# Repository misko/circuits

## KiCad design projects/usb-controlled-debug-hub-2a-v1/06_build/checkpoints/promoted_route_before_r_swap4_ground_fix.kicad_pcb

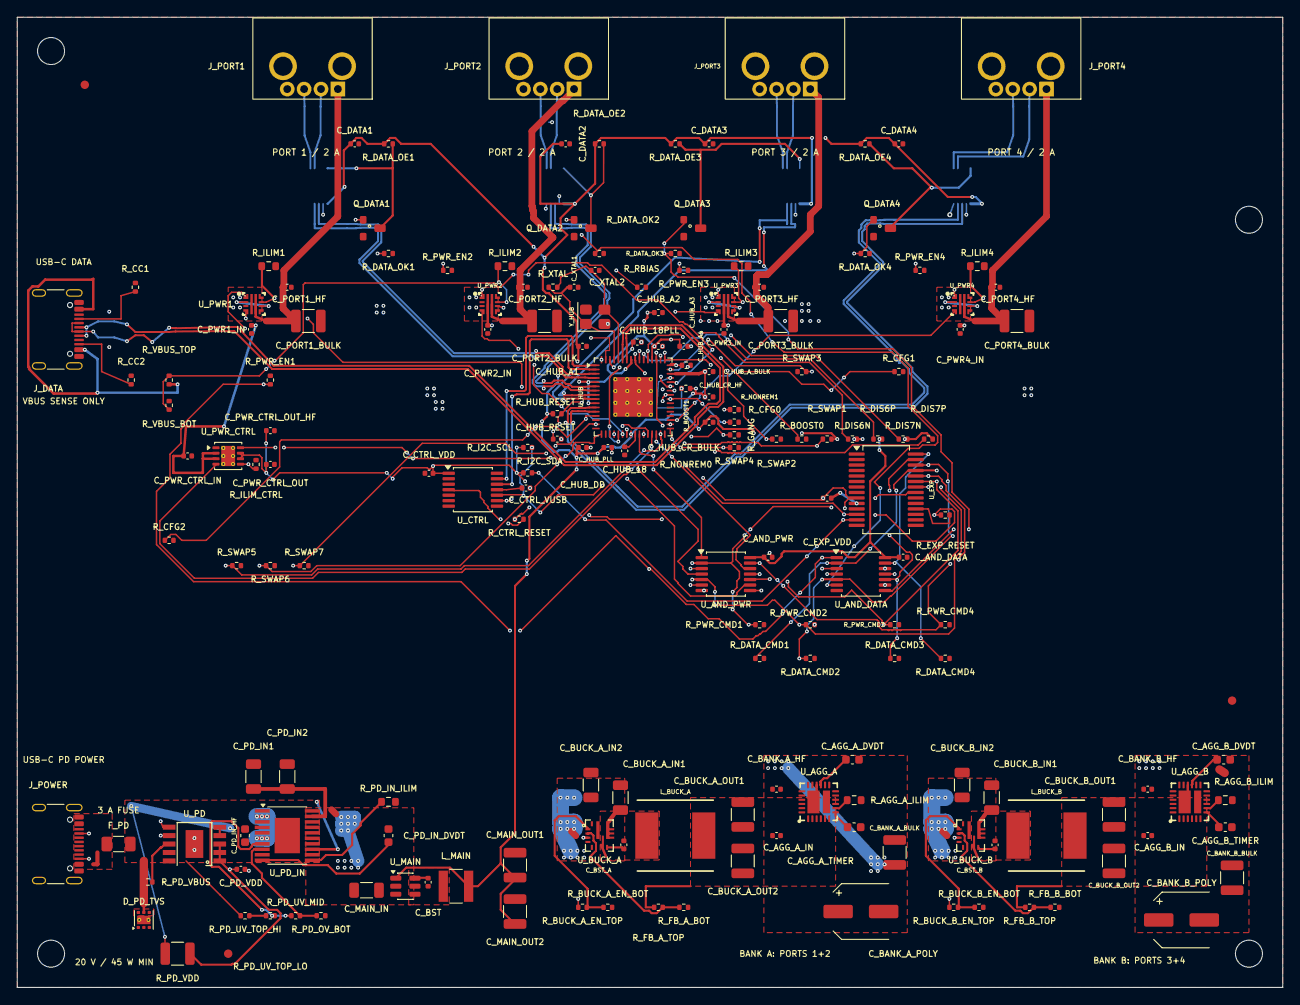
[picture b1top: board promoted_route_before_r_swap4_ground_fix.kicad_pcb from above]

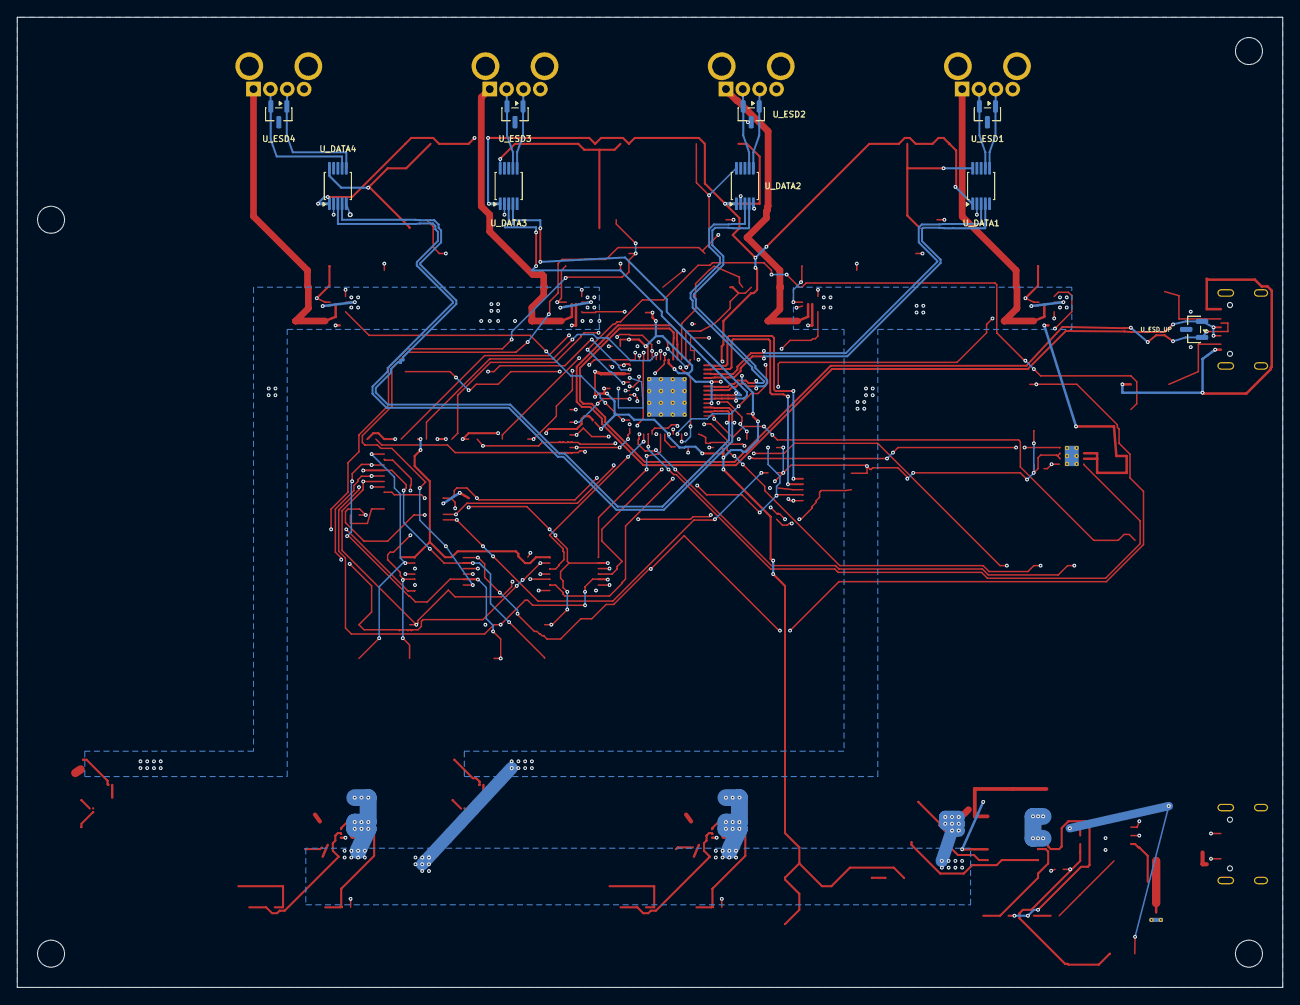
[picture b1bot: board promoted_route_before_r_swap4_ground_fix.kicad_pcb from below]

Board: 4 copper layers, 150.0 x 115.0 mm, 190 parts (9 on the bottom side), 129 nets.

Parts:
C_AGG_A_DVDT: 3.3nF; C_0603_1608Metric
C_AGG_A_IN: 100nF; C_0402_1005Metric
C_AGG_A_TIMER: 6.8nF; C_0603_1608Metric
C_AGG_B_DVDT: 3.3nF; C_0603_1608Metric
C_AGG_B_IN: 100nF; C_0402_1005Metric
C_AGG_B_TIMER: 6.8nF; C_0603_1608Metric
C_AND_DATA: 100nF; C_0402_1005Metric
C_AND_PWR: 100nF; C_0402_1005Metric
C_BANK_A_BULK: 22uF; C_1210_3225Metric
C_BANK_A_HF: 100nF; C_0402_1005Metric
C_BANK_A_POLY: 180uF; Panasonic_C6_6.3x5.9
C_BANK_B_BULK: 22uF; C_1210_3225Metric
C_BANK_B_HF: 100nF; C_0402_1005Metric
C_BANK_B_POLY: 180uF; Panasonic_C6_6.3x5.9
C_BST: 100nF; C_0402_1005Metric
C_BST_A: 100nF; C_0402_1005Metric
C_BST_B: 100nF; C_0402_1005Metric
C_BUCK_A_IN1, C_BUCK_A_IN2: 10uF; C_1206_3216Metric
C_BUCK_A_OUT1, C_BUCK_A_OUT2: 22uF; C_1210_3225Metric
C_BUCK_B_IN1, C_BUCK_B_IN2: 10uF; C_1206_3216Metric
C_BUCK_B_OUT1, C_BUCK_B_OUT2: 22uF; C_1210_3225Metric
C_CTRL_VDD: 100nF; C_0402_1005Metric
C_CTRL_VUSB: 330nF; C_0402_1005Metric
C_DATA1, C_DATA2, C_DATA3, C_DATA4: 100nF; C_0402_1005Metric
C_EXP_VDD: 100nF; C_0402_1005Metric
C_HUB_18, C_HUB_18PLL: 1uF; C_0402_1005Metric
C_HUB_A1, C_HUB_A2, C_HUB_A3, C_HUB_A4: 100nF; C_0402_1005Metric
C_HUB_A_BULK: 1uF; C_0402_1005Metric
C_HUB_CR_BULK: 1uF; C_0402_1005Metric
C_HUB_CR_HF: 100nF; C_0402_1005Metric
C_HUB_DD: 100nF; C_0402_1005Metric
C_HUB_PLL: 100nF; C_0402_1005Metric
C_HUB_RESET: 1uF; C_0402_1005Metric
C_MAIN_IN: 10uF; C_1206_3216Metric
C_MAIN_OUT1, C_MAIN_OUT2: 22uF; C_1210_3225Metric
C_PD_IN1, C_PD_IN2: 10uF; C_1206_3216Metric
C_PD_IN_DVDT: 3.3nF; C_0603_1608Metric
C_PD_IN_HF: 1uF; C_0603_1608Metric
C_PD_VDD: 1uF; C_0402_1005Metric
C_PORT1_BULK, C_PORT2_BULK, C_PORT3_BULK, C_PORT4_BULK: 22uF; C_1210_3225Metric
C_PORT1_HF, C_PORT2_HF, C_PORT3_HF, C_PORT4_HF: 100nF; C_0402_1005Metric
C_PWR1_IN, C_PWR2_IN, C_PWR3_IN, C_PWR4_IN: 100nF; C_0402_1005Metric
C_PWR_CTRL_IN: 100nF; C_0402_1005Metric
C_PWR_CTRL_OUT: 1uF; C_0402_1005Metric
C_PWR_CTRL_OUT_HF: 100nF; C_0402_1005Metric
C_XTAL1, C_XTAL2: 18pF; C_0402_1005Metric
D_PD_TVS: C523793; WSON-6-1EP_2x2mm_P0.65mm_EP1x1.6mm_ThermalVias
FID1, FID2, FID3: Fiducial_1mm_Mask2mm
F_PD: C14165; Fuse_1206_3216Metric
H1, H2, H3, H4: MountingHole_3.2mm_M3
J_DATA: C165948; TYPE-C-31-M-12_Datasheet
J_PORT1, J_PORT2, J_PORT3, J_PORT4: USB1130-15-A; USB_A_GCT_USB1130-15-A_Horizontal
J_POWER: C165948; TYPE-C-31-M-12_Datasheet
L_BUCK_A: C17700166; Sunlord_MWSA0804S
L_BUCK_B: C17700166; Sunlord_MWSA0804S
L_MAIN: C15269; Sunlord_SWPA4030S
Q_DATA1, Q_DATA2, Q_DATA3, Q_DATA4: C85047; Diodes_SOT23_2N7002K
R_AGG_A_ILIM: 300Ω; R_0603_1608Metric
R_AGG_B_ILIM: 300Ω; R_0603_1608Metric
R_BOOST0, R_BOOST1: 10kΩ; R_0402_1005Metric
R_BUCK_A_EN_BOT: 27.4kΩ; R_0402_1005Metric
R_BUCK_A_EN_TOP: 200kΩ; R_0402_1005Metric
R_BUCK_B_EN_BOT: 27.4kΩ; R_0402_1005Metric
R_BUCK_B_EN_TOP: 200kΩ; R_0402_1005Metric
R_CC1, R_CC2: 5.1kΩ; R_0402_1005Metric
R_CFG0, R_CFG1, R_CFG2: 10kΩ; R_0402_1005Metric
R_CTRL_RESET: 10kΩ; R_0402_1005Metric
R_DATA_CMD1, R_DATA_CMD2, R_DATA_CMD3, R_DATA_CMD4: 10kΩ; R_0402_1005Metric
R_DATA_OE1, R_DATA_OE2, R_DATA_OE3, R_DATA_OE4: 10kΩ; R_0402_1005Metric
R_DATA_OK1, R_DATA_OK2, R_DATA_OK3, R_DATA_OK4: 10kΩ; R_0402_1005Metric
R_DIS6N, R_DIS6P, R_DIS7N, R_DIS7P: 10kΩ; R_0402_1005Metric
R_EXP_RESET: 10kΩ; R_0402_1005Metric
R_FB_A_BOT: 10kΩ; R_0402_1005Metric
R_FB_A_TOP: 75kΩ; R_0402_1005Metric
R_FB_B_BOT: 10kΩ; R_0402_1005Metric
R_FB_B_TOP: 75kΩ; R_0402_1005Metric
R_GANG: 10kΩ; R_0402_1005Metric
R_HUB_RESET: 10kΩ; R_0402_1005Metric
R_I2C_SCL, R_I2C_SDA: 4.7kΩ; R_0402_1005Metric
R_ILIM1, R_ILIM2, R_ILIM3, R_ILIM4: 1.4kΩ; R_0603_1608Metric
R_ILIM_CTRL: 187kΩ; R_0402_1005Metric
R_NONREM0, R_NONREM1: 10kΩ; R_0402_1005Metric
R_PD_IN_ILIM: 5.9kΩ; R_0603_1608Metric
R_PD_OV_BOT: 51kΩ; R_0402_1005Metric
R_PD_UV_MID: 20kΩ; R_0402_1005Metric
R_PD_UV_TOP_HI: 910kΩ; R_0402_1005Metric
R_PD_UV_TOP_LO: 22kΩ; R_0402_1005Metric
R_PD_VBUS: 10kΩ; R_0402_1005Metric
R_PD_VDD: 1kΩ; R_1210_3225Metric
R_PWR_CMD1, R_PWR_CMD2, R_PWR_CMD3, R_PWR_CMD4: 10kΩ; R_0402_1005Metric
R_PWR_EN1, R_PWR_EN2, R_PWR_EN3, R_PWR_EN4: 10kΩ; R_0402_1005Metric
R_RBIAS: 12kΩ; R_0402_1005Metric
R_SWAP1, R_SWAP2, R_SWAP3, R_SWAP4, R_SWAP5, R_SWAP6, R_SWAP7: 100kΩ; R_0402_1005Metric
R_VBUS_BOT: 100kΩ; R_0402_1005Metric
R_VBUS_TOP: 47kΩ; R_0402_1005Metric
R_XTAL: 1MΩ; R_0402_1005Metric
U_AGG_A: C2155765; TI_TPS25982_RGE0024_SplitPad_ThermalVias
U_AGG_B: C2155765; TI_TPS25982_RGE0024_SplitPad_ThermalVias
U_AND_DATA: C6053; TSSOP-14_4.4x5mm_P0.65mm
U_AND_PWR: C6053; TSSOP-14_4.4x5mm_P0.65mm
U_BUCK_A: C841386; TI_RPA0010A_VQFN-HR-10_3x3mm
U_BUCK_B: C841386; TI_RPA0010A_VQFN-HR-10_3x3mm
U_CTRL: C130462; TSSOP-14_4.4x5mm_P0.65mm
U_DATA1, U_DATA2, U_DATA3, U_DATA4: C11355; MSOP-10_3x3mm_P0.5mm
U_ESD1, U_ESD2, U_ESD3, U_ESD4: C3709087; SOT-23
U_ESD_UP: C3709087; SOT-23
U_EXP: C558584; SSOP-28_5.3x10.2mm_P0.65mm
U_HUB: C478081; QFN-64-1EP_9x9mm_P0.5mm_EP4.7x4.7mm_ThermalVias
U_MAIN: C5248536; TSOT-23-6
U_PD: C970725; WCH_CH224K_ESSOP10_EP
U_PD_IN: C1849461; Texas_PWP0020A
U_PWR1, U_PWR2, U_PWR3, U_PWR4: C3662799; TI_RPW0010A_VQFN-HR-10_2x2mm_P0.45mm
U_PWR_CTRL: C130056; VSON-8-1EP_3x3mm_P0.65mm_EP1.65x2.4mm_ThermalVias
Y_HUB: C70590; Crystal_SMD_3225-4Pin_3.2x2.5mm

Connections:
3V3_MAIN: C_AND_DATA.1, C_AND_PWR.1, C_DATA1.1, C_DATA2.1, C_DATA3.1, C_DATA4.1, C_HUB_A1.1, C_HUB_A2.1, C_HUB_A3.1, C_HUB_A4.1, C_HUB_A_BULK.1, C_HUB_CR_BULK.1, C_HUB_CR_HF.1, C_HUB_DD.1, C_HUB_PLL.1, C_MAIN_OUT1.1, C_MAIN_OUT2.1, L_MAIN.2, R_DATA_OE1.1, R_DATA_OE2.1, R_DATA_OE3.1, R_DATA_OE4.1, R_DIS6N.1, R_DIS6P.1, R_DIS7N.1, R_DIS7P.1, R_HUB_RESET.1, R_NONREM0.1, R_SWAP1.2, U_AND_DATA.14, U_AND_PWR.14, U_DATA1.1, U_DATA2.1, U_DATA3.1, U_DATA4.1, U_HUB.5, U_HUB.10, U_HUB.24, U_HUB.46, U_HUB.52, U_HUB.57, U_HUB.64, U_MAIN.1
AGG_A_DVDT: C_AGG_A_DVDT.1, U_AGG_A.15
AGG_A_ILIM: R_AGG_A_ILIM.1, U_AGG_A.8
AGG_A_TIMER: C_AGG_A_TIMER.1, U_AGG_A.7
AGG_B_DVDT: C_AGG_B_DVDT.1, U_AGG_B.15
AGG_B_ILIM: R_AGG_B_ILIM.1, U_AGG_B.8
AGG_B_TIMER: C_AGG_B_TIMER.1, U_AGG_B.7
BOOT_A: C_BST_A.1, U_BUCK_A.7
BOOT_B: C_BST_B.1, U_BUCK_B.7
BST_3V3: C_BST.1, U_MAIN.6
BUCK_A_EN: R_BUCK_A_EN_BOT.1, R_BUCK_A_EN_TOP.2, U_BUCK_A.1
BUCK_B_EN: R_BUCK_B_EN_BOT.1, R_BUCK_B_EN_TOP.2, U_BUCK_B.1
CTRL_RESET_N: R_CTRL_RESET.2, U_CTRL.4
CTRL_VUSB_3V3: C_CTRL_VUSB.1, U_CTRL.11
DATA_CC1: J_DATA.A5, R_CC1.1
DATA_CC2: J_DATA.B5, R_CC2.1
DATA_CMD1: R_DATA_CMD1.1, U_AND_DATA.2, U_EXP.25
DATA_CMD2: R_DATA_CMD2.1, U_AND_DATA.5, U_EXP.26
DATA_CMD3: R_DATA_CMD3.1, U_AND_DATA.10, U_EXP.27
DATA_CMD4: R_DATA_CMD4.1, U_AND_DATA.13, U_EXP.28
DATA_OE1_N: Q_DATA1.3, R_DATA_OE1.2, U_DATA1.10
DATA_OE2_N: Q_DATA2.3, R_DATA_OE2.2, U_DATA2.10
DATA_OE3_N: Q_DATA3.3, R_DATA_OE3.2, U_DATA3.10
DATA_OE4_N: Q_DATA4.3, R_DATA_OE4.2, U_DATA4.10
DATA_OK1: Q_DATA1.1, R_DATA_OK1.1, U_AND_DATA.3
DATA_OK2: Q_DATA2.1, R_DATA_OK2.1, U_AND_DATA.6
DATA_OK3: Q_DATA3.1, R_DATA_OK3.1, U_AND_DATA.8
DATA_OK4: Q_DATA4.1, R_DATA_OK4.1, U_AND_DATA.11
EXP_RESET_N: R_EXP_RESET.2, U_EXP.18
FB_A: R_FB_A_BOT.1, R_FB_A_TOP.2, U_BUCK_A.2
FB_B: R_FB_B_BOT.1, R_FB_B_TOP.2, U_BUCK_B.2
GND: C_AGG_A_DVDT.2, C_AGG_A_IN.2, C_AGG_A_TIMER.2, C_AGG_B_DVDT.2, C_AGG_B_IN.2, C_AGG_B_TIMER.2, C_AND_DATA.2, C_AND_PWR.2, C_BANK_A_BULK.2, C_BANK_A_HF.2, C_BANK_A_POLY.2, C_BANK_B_BULK.2, C_BANK_B_HF.2, C_BANK_B_POLY.2, C_BUCK_A_IN1.2, C_BUCK_A_IN2.2, C_BUCK_A_OUT1.2, C_BUCK_A_OUT2.2, C_BUCK_B_IN1.2, C_BUCK_B_IN2.2, C_BUCK_B_OUT1.2, C_BUCK_B_OUT2.2, C_CTRL_VDD.2, C_CTRL_VUSB.2, C_DATA1.2, C_DATA2.2, C_DATA3.2, C_DATA4.2, C_EXP_VDD.2, C_HUB_18.2, C_HUB_18PLL.2, C_HUB_A1.2, C_HUB_A2.2, C_HUB_A3.2, C_HUB_A4.2, C_HUB_A_BULK.2, C_HUB_CR_BULK.2, C_HUB_CR_HF.2, C_HUB_DD.2, C_HUB_PLL.2, C_HUB_RESET.2, C_MAIN_IN.2, C_MAIN_OUT1.2, C_MAIN_OUT2.2, C_PD_IN1.2, C_PD_IN2.2, C_PD_IN_DVDT.2, C_PD_IN_HF.2, C_PD_VDD.2, C_PORT1_BULK.2, C_PORT1_HF.2, C_PORT2_BULK.2, C_PORT2_HF.2, C_PORT3_BULK.2, C_PORT3_HF.2, C_PORT4_BULK.2, C_PORT4_HF.2, C_PWR1_IN.2, C_PWR2_IN.2, C_PWR3_IN.2, C_PWR4_IN.2, C_PWR_CTRL_IN.2, C_PWR_CTRL_OUT.2, C_PWR_CTRL_OUT_HF.2, C_XTAL1.2, C_XTAL2.2, D_PD_TVS.1, D_PD_TVS.2, D_PD_TVS.3, D_PD_TVS.7, J_DATA.A1, J_DATA.A12, J_DATA.B1, J_DATA.B12, J_DATA.SH, J_PORT1.4, J_PORT1.5, J_PORT2.4, J_PORT2.5, J_PORT3.4, J_PORT3.5, J_PORT4.4, J_PORT4.5, J_POWER.A1, J_POWER.A12, J_POWER.B1, J_POWER.B12, J_POWER.SH, Q_DATA1.2, Q_DATA2.2, Q_DATA3.2, Q_DATA4.2, R_AGG_A_ILIM.2, R_AGG_B_ILIM.2, R_BOOST0.2, R_BOOST1.2, R_BUCK_A_EN_BOT.2, R_BUCK_B_EN_BOT.2, R_CC1.2, R_CC2.2, R_CFG0.2, R_CFG1.2, R_CFG2.2, R_DATA_CMD1.2, R_DATA_CMD2.2, R_DATA_CMD3.2, R_DATA_CMD4.2, R_DATA_OK1.2, R_DATA_OK2.2, R_DATA_OK3.2, R_DATA_OK4.2, R_FB_A_BOT.2, R_FB_B_BOT.2, R_GANG.2, R_ILIM1.2, R_ILIM2.2, R_ILIM3.2, R_ILIM4.2, R_ILIM_CTRL.2, R_NONREM1.2, R_PD_IN_ILIM.2, R_PD_OV_BOT.2, R_PWR_CMD1.2, R_PWR_CMD2.2, R_PWR_CMD3.2, R_PWR_CMD4.2, R_PWR_EN1.2, R_PWR_EN2.2, R_PWR_EN3.2, R_PWR_EN4.2, R_RBIAS.2, R_SWAP2.2, R_SWAP3.2, R_SWAP4.2, R_SWAP5.2, R_SWAP6.2, R_SWAP7.2, R_VBUS_BOT.2, U_AGG_A.4, U_AGG_A.5, U_AGG_A.10, U_AGG_A.11, U_AGG_A.12, U_AGG_A.14, U_AGG_A.26, U_AGG_B.4, U_AGG_B.5, U_AGG_B.10, U_AGG_B.11, U_AGG_B.12, U_AGG_B.14, U_AGG_B.26, U_AND_DATA.7, U_AND_PWR.7, U_BUCK_A.3, U_BUCK_A.9, U_BUCK_A.10, U_BUCK_B.3, U_BUCK_B.9, U_BUCK_B.10, U_CTRL.14, U_DATA1.2, U_DATA1.5, U_DATA2.2, U_DATA2.5, U_DATA3.2, U_DATA3.5, U_DATA4.2, U_DATA4.5, U_ESD1.3, U_ESD2.3, U_ESD3.3, U_ESD4.3, U_ESD_UP.3, U_EXP.10, U_EXP.15, U_EXP.16, U_EXP.17, U_HUB.65, U_MAIN.4, U_PD.9, U_PD.11, U_PD_IN.9, U_PD_IN.12, U_PD_IN.21, U_PWR1.2, U_PWR1.8, U_PWR2.2, U_PWR2.8, U_PWR3.2, U_PWR3.8, U_PWR4.2, U_PWR4.8, U_PWR_CTRL.1, U_PWR_CTRL.9, Y_HUB.2, Y_HUB.4
HUB_BOOST0: R_BOOST0.1, U_HUB.50
HUB_BOOST1: R_BOOST1.1, U_HUB.48
HUB_CFG0: R_CFG0.1, U_HUB.41
HUB_CFG1: R_CFG1.1, U_HUB.42
HUB_CFG2: R_CFG2.1, U_HUB.13
HUB_DIS6_N: R_DIS6N.2, U_HUB.53
HUB_DIS6_P: R_DIS6P.2, U_HUB.54
HUB_DIS7_N: R_DIS7N.2, U_HUB.55
HUB_DIS7_P: R_DIS7P.2, U_HUB.56
HUB_GANG: R_GANG.1, U_HUB.34
HUB_NONREM0: R_NONREM0.2, U_HUB.45
HUB_NONREM1: R_NONREM1.1, U_HUB.40
HUB_OCS1_N: U_HUB.28, U_PWR_CTRL.8
HUB_OCS2_N: U_HUB.27, U_PWR1.4
HUB_OCS3_N: U_HUB.22, U_PWR2.4
HUB_OCS4_N: U_HUB.21, U_PWR3.4
HUB_OCS5_N: U_HUB.35, U_PWR4.4
HUB_PRTPWR1: U_HUB.29, U_PWR_CTRL.4
HUB_PRTPWR2: U_AND_PWR.1, U_HUB.26
HUB_PRTPWR3: U_AND_PWR.4, U_HUB.23
HUB_PRTPWR4: U_AND_PWR.9, U_HUB.20
HUB_PRTPWR5: U_AND_PWR.12, U_HUB.30
HUB_RESET_N: C_HUB_RESET.1, R_HUB_RESET.2, U_HUB.43
HUB_SWAP1: R_SWAP1.1, U_HUB.51
HUB_SWAP2: R_SWAP2.1, U_HUB.49
HUB_SWAP3: R_SWAP3.1, U_HUB.47
HUB_SWAP4: R_SWAP4.1, U_HUB.33
HUB_SWAP5: R_SWAP5.1, U_HUB.31
HUB_SWAP6: R_SWAP6.1, U_HUB.17
HUB_SWAP7: R_SWAP7.1, U_HUB.15
HUB_VBUS_SENSE: R_VBUS_BOT.1, R_VBUS_TOP.2, U_HUB.44
HUB_VDD18: C_HUB_18.1, U_HUB.25
HUB_VDD18PLL: C_HUB_18PLL.1, U_HUB.62
I2C_SCL: R_I2C_SCL.2, U_CTRL.10, U_EXP.12
I2C_SDA: R_I2C_SDA.2, U_CTRL.9, U_EXP.13
ILIM1: R_ILIM1.1, U_PWR1.9
ILIM2: R_ILIM2.1, U_PWR2.9
ILIM3: R_ILIM3.1, U_PWR3.9
ILIM4: R_ILIM4.1, U_PWR4.9
ILIM_CTRL: R_ILIM_CTRL.1, U_PWR_CTRL.5
MGMT_N: U_CTRL.12, U_HUB.2
MGMT_P: U_CTRL.13, U_HUB.1
P1_HUB_N: U_DATA1.3, U_HUB.3
P1_HUB_P: U_DATA1.4, U_HUB.4
P1_PORT_N: J_PORT1.2, U_DATA1.7, U_ESD1.2
P1_PORT_P: J_PORT1.3, U_DATA1.6, U_ESD1.1
P2_HUB_N: U_DATA2.3, U_HUB.6
P2_HUB_P: U_DATA2.4, U_HUB.7
P2_PORT_N: J_PORT2.2, U_DATA2.7, U_ESD2.2
P2_PORT_P: J_PORT2.3, U_DATA2.6, U_ESD2.1
P3_HUB_N: U_DATA3.3, U_HUB.8
P3_HUB_P: U_DATA3.4, U_HUB.9
P3_PORT_N: J_PORT3.2, U_DATA3.7, U_ESD3.2
P3_PORT_P: J_PORT3.3, U_DATA3.6, U_ESD3.1
P4_HUB_N: U_DATA4.3, U_HUB.11
P4_HUB_P: U_DATA4.4, U_HUB.12
P4_PORT_N: J_PORT4.2, U_DATA4.7, U_ESD4.2
P4_PORT_P: J_PORT4.3, U_DATA4.6, U_ESD4.1
P5V_A_PROTECTED: C_BANK_A_BULK.1, C_BANK_A_HF.1, C_BANK_A_POLY.1, C_PWR1_IN.1, C_PWR2_IN.1, C_PWR_CTRL_IN.1, U_AGG_A.17, U_AGG_A.18, U_AGG_A.19, U_AGG_A.20, U_AGG_A.21, U_AGG_A.22, U_AGG_A.23, U_AGG_A.24, U_PWR1.5, U_PWR2.5, U_PWR_CTRL.2, U_PWR_CTRL.3
P5V_BANK_A: C_AGG_A_IN.1, C_BUCK_A_OUT1.1, C_BUCK_A_OUT2.1, L_BUCK_A.2, R_FB_A_TOP.1, U_AGG_A.1, U_AGG_A.2, U_AGG_A.3, U_AGG_A.6, U_AGG_A.16, U_AGG_A.25
P5V_BANK_B: C_AGG_B_IN.1, C_BUCK_B_OUT1.1, C_BUCK_B_OUT2.1, L_BUCK_B.2, R_FB_B_TOP.1, U_AGG_B.1, U_AGG_B.2, U_AGG_B.3, U_AGG_B.6, U_AGG_B.16, U_AGG_B.25
P5V_B_PROTECTED: C_BANK_B_BULK.1, C_BANK_B_HF.1, C_BANK_B_POLY.1, C_PWR3_IN.1, C_PWR4_IN.1, U_AGG_B.17, U_AGG_B.18, U_AGG_B.19, U_AGG_B.20, U_AGG_B.21, U_AGG_B.22, U_AGG_B.23, U_AGG_B.24, U_PWR3.5, U_PWR4.5
PD_CC1: J_POWER.A5, U_PD.7
PD_CC2: J_POWER.B5, U_PD.6
PD_IN_DVDT: C_PD_IN_DVDT.1, U_PD_IN.10
PD_IN_ILIM: R_PD_IN_ILIM.1, U_PD_IN.11
PD_IN_OV: R_PD_OV_BOT.1, R_PD_UV_MID.2, U_PD_IN.8
PD_IN_UV: R_PD_UV_MID.1, R_PD_UV_TOP_LO.2, U_PD_IN.7
PD_PROTO: U_PD.4, U_PD.5
PD_UV_TOP_MID: R_PD_UV_TOP_HI.2, R_PD_UV_TOP_LO.1
PD_VBUS_SENSE: R_PD_VBUS.2, U_PD.8
PD_VDD: C_PD_VDD.1, R_PD_VDD.2, U_PD.1, U_PD.2, U_PD.3
PWR_CMD1: R_PWR_CMD1.1, U_AND_PWR.2, U_EXP.21
PWR_CMD2: R_PWR_CMD2.1, U_AND_PWR.5, U_EXP.22
PWR_CMD3: R_PWR_CMD3.1, U_AND_PWR.10, U_EXP.23
PWR_CMD4: R_PWR_CMD4.1, U_AND_PWR.13, U_EXP.24
PWR_EN1: R_PWR_EN1.1, U_AND_DATA.1, U_AND_PWR.3, U_PWR1.1
PWR_EN2: R_PWR_EN2.1, U_AND_DATA.4, U_AND_PWR.6, U_PWR2.1
PWR_EN3: R_PWR_EN3.1, U_AND_DATA.9, U_AND_PWR.8, U_PWR3.1
PWR_EN4: R_PWR_EN4.1, U_AND_DATA.12, U_AND_PWR.11, U_PWR4.1
RBIAS: R_RBIAS.1, U_HUB.63
SW_3V3: C_BST.2, L_MAIN.1, U_MAIN.5
SW_A: C_BST_A.2, L_BUCK_A.1, U_BUCK_A.6
SW_B: C_BST_B.2, L_BUCK_B.1, U_BUCK_B.6
UP_HUB_N: J_DATA.A7, J_DATA.B7, U_ESD_UP.1, U_HUB.58
UP_HUB_P: J_DATA.A6, J_DATA.B6, U_ESD_UP.2, U_HUB.59
USB_UP_VBUS: J_DATA.A4, J_DATA.A9, J_DATA.B4, J_DATA.B9, R_VBUS_TOP.1
VBUS1_SW: C_PORT1_BULK.1, C_PORT1_HF.1, J_PORT1.1, U_PWR1.6
VBUS2_SW: C_PORT2_BULK.1, C_PORT2_HF.1, J_PORT2.1, U_PWR2.6
VBUS3_SW: C_PORT3_BULK.1, C_PORT3_HF.1, J_PORT3.1, U_PWR3.6
VBUS4_SW: C_PORT4_BULK.1, C_PORT4_HF.1, J_PORT4.1, U_PWR4.6
VBUS_CTRL: C_CTRL_VDD.1, C_EXP_VDD.1, C_PWR_CTRL_OUT.1, C_PWR_CTRL_OUT_HF.1, R_CTRL_RESET.1, R_EXP_RESET.1, R_I2C_SCL.1, R_I2C_SDA.1, U_CTRL.1, U_EXP.9, U_PWR_CTRL.6, U_PWR_CTRL.7
VBUS_PD: C_PD_IN_HF.1, D_PD_TVS.4, D_PD_TVS.5, D_PD_TVS.6, F_PD.2, R_PD_UV_TOP_HI.1, R_PD_VBUS.1, R_PD_VDD.1, U_PD_IN.1, U_PD_IN.2, U_PD_IN.6, U_PD_IN.13
VBUS_PD_PROTECTED: C_BUCK_A_IN1.1, C_BUCK_A_IN2.1, C_BUCK_B_IN1.1, C_BUCK_B_IN2.1, C_MAIN_IN.1, C_PD_IN1.1, C_PD_IN2.1, R_BUCK_A_EN_TOP.1, R_BUCK_B_EN_TOP.1, U_BUCK_A.8, U_BUCK_B.8, U_MAIN.2, U_MAIN.3, U_PD_IN.18, U_PD_IN.19
VBUS_PD_RAW: F_PD.1, J_POWER.A4, J_POWER.A9, J_POWER.B4, J_POWER.B9
XTAL1: C_XTAL1.1, R_XTAL.1, U_HUB.61, Y_HUB.1
XTAL2: C_XTAL2.1, R_XTAL.2, U_HUB.60, Y_HUB.3
